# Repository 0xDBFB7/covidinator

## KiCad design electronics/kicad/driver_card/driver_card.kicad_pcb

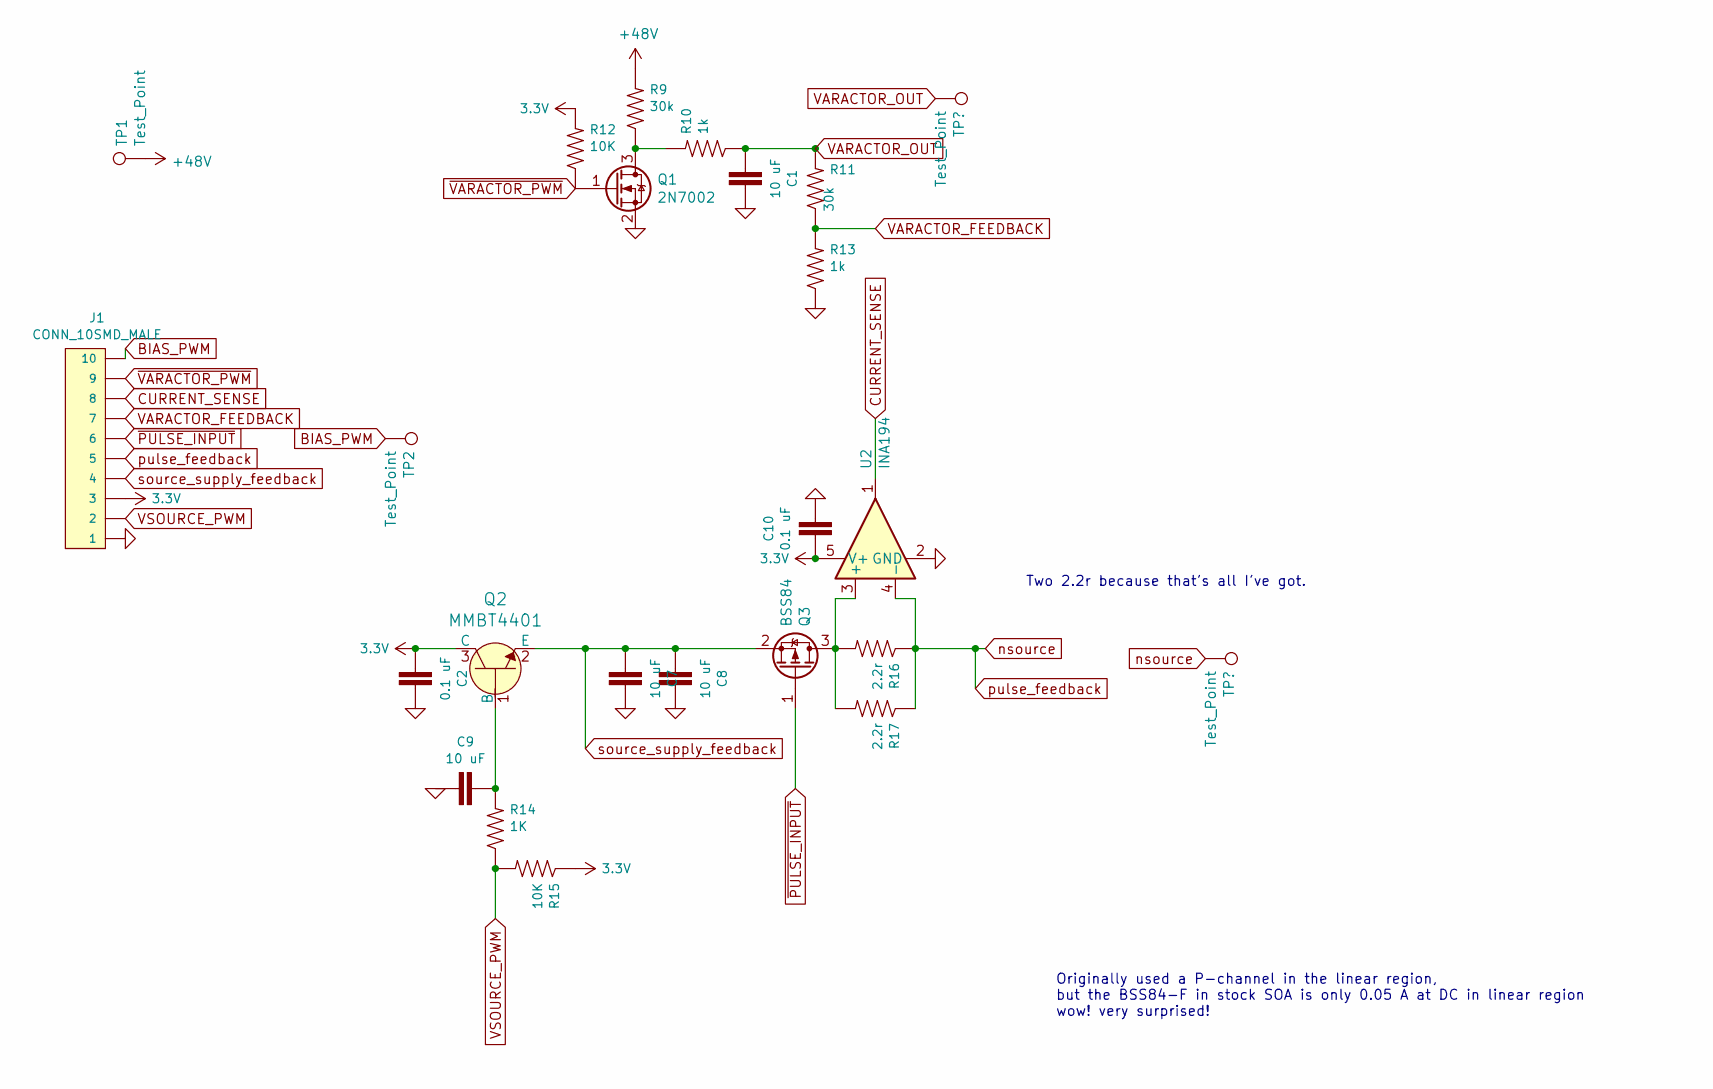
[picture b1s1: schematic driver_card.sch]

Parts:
C1, C7, C8, C9: 10 uF; 0603
C2, C10: 0.1 uF; 0603
J1: CONN_10SMD_MALE; 1X10_SMD_MALE
Q1: 2N7002; SOT-23
Q2: MMBT4401; SOT-23-3; MPN MMBT4401; Digi-Key_PN MMBT4401FSCT-ND
Q3: BSS84; SOT-23
R9, R11: 30k; R_0603_1608Metric
R10, R13: 1k; R_0603_1608Metric
R12: 10K; R_0603_1608Metric
R14: 1K; R_0402_1005Metric
R15: 10K; R_0402_1005Metric
R16, R17: 2.2r; R_0805_2012Metric
TP1, TP2: Test_Point; TestPoint_Pad_2.0x2.0mm
U2: INA194; SOT-23-5

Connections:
3.3V: C2.2, C10.2, J1.3, Q2.3 (C), R12.2, R15.1, U2.5 (V+)
+48V: R9.2, TP1.1
BIAS_PWM: J1.10, TP2.1
CURRENT_SENSE: J1.8, U2.1
GND: C1.1, C2.1, C7.1, C8.1, C9.2, C10.1, J1.1, Q1.2 (S), R13.1, U2.2 (GND)
unnamed: C9.1, Q2.1 (B), R14.2
unnamed: Q1.3 (D), R9.1, R10.2
unnamed: Q3.3 (D), R16.2, R17.2, U2.3 (+)
VARACTOR_FEEDBACK: J1.7, R11.1, R13.2
VARACTOR_OUT: C1.2, R10.1, R11.2; also elsewhere on the board
VSOURCE_PWM: J1.2, R14.1, R15.2
nsource: J1.5, R16.1, R17.1, U2.4 (-); also elsewhere on the board
source_supply_feedback: C7.2, C8.2, J1.4, Q2.2 (E), Q3.2 (S)
~PULSE_INPUT: J1.6, Q3.1 (G)
~VARACTOR_PWM: J1.9, Q1.1 (G), R12.1

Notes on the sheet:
Two 2.2r because that's all I've got.
Originally used a P-channel in the linear region, but the BSS84-F in stock SOA is only 0.05 A at DC in linear region wow! very surprised!

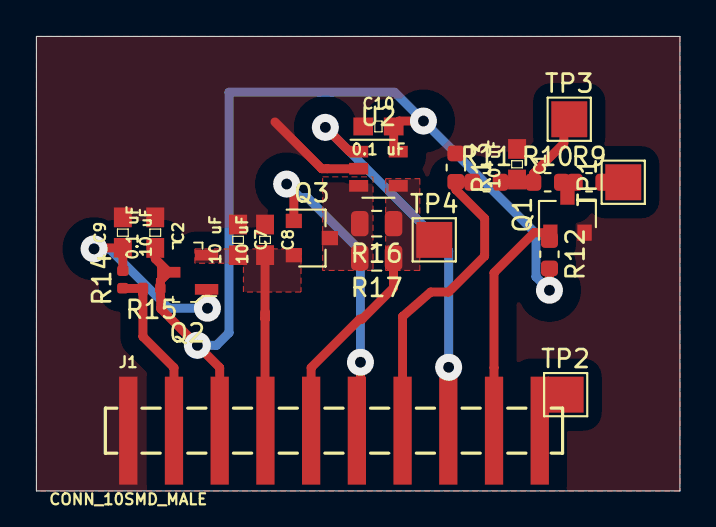
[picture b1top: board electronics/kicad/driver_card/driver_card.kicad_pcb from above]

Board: 2 copper layers, 35.8 x 25.2 mm, 24 parts (0 on the bottom side), 15 nets.

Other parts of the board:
TP3, TP4: Test_Point; TestPoint_Pad_2.0x2.0mm

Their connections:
VARACTOR_OUT: TP3.1; also elsewhere on the board
nsource: TP4.1; also elsewhere on the board

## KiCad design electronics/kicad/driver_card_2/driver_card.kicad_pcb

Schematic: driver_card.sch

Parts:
C1, C2, C3, C8, C10, C11: 0.1 uF; 0603
C4, C9: 10 uF; 0603
C5, C6, C7: 10uF; 1206
J1: CONN_10SMD_MALE; 1X10_SMD_MALE
Q1, Q2, Q4: 2N7002; SOT-23
Q3: BSS84; SOT-23
R1, R9, R11: 30k; R_0603_1608Metric
R2, R18, R19: 10k; R_0603_1608Metric
R3, R7, R8: 5k; R_0603_1608Metric
R4, R10: 1K; R_0603_1608Metric
R5, R6: 2k; R_0603_1608Metric
R12, R13, R14, R15, R17: 1k; R_0603_1608Metric
R16: 0.1R; R_0805_2012Metric
TP1: 48V; TestPoint_Pad_2.0x2.0mm
TP2: 12V; TestPoint_Pad_2.0x2.0mm
TP3, TP4: Test_Point; TestPoint_Pad_2.0x2.0mm
U1: MCP4725SOT-23; SOT23-6
U2: INA194; SOT-23-5
U3: AZ1117CH-3_3TRG1; SOT-223; MPN AZ1117CH-3.3TRG1; Digi-Key_PN AZ1117CH-3.3TRG1DICT-ND
U4: MCP1416T-E_OT; SOT-753; MPN MCP1416T-E/OT; Digi-Key_PN MCP1416T-E/OTCT-ND

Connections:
3.3V: C10.2, J1.3, R5.2, R13.2, U2.5 (V+)
+12V: C2.2, C5.1, R1.2, TP2.1, U3.3, U4.2 (VDD)
+48V: C3.2, R9.2, TP1.1
BIAS_OUT: C11.2, Q4.3 (D), R18.1, R19.2
BIAS_PWM: J1.10, R12.1
CURRENT_SENSE: J1.8, U2.1
GND: C1.1, C2.1, C3.1, C4.1, C5.2, C6.2, C7.2, C8.1, C9.1, C10.1, C11.1, J1.1, Q1.2 (S), Q2.2 (S), Q4.2 (S), R4.1, R6.1, R10.1, R11.1, R17.1, R19.1, U2.2 (GND), U4.4 (GND)
unnamed: C4.2, Q1.1 (G), R5.1, R6.2, R7.2
unnamed: C6.1, R1.1, R2.2, U3.1
unnamed: C7.1, C8.2, Q3.2 (S), R3.2, U3.2, U3.4
unnamed: C9.2, Q4.1 (G), R12.2, R14.1, R15.2
unnamed: Q2.3 (D), R2.1
unnamed: Q3.1 (G), U4.5 (OUT)
unnamed: Q3.3 (D), R16.2, U2.3 (+)
unnamed: R13.1, R14.2
unnamed: R15.1, R17.2
VARACTOR_FEEDBACK: J1.7
VARACTOR_OUT: C1.2, Q1.3 (D), R9.1, R11.2, TP3.1
VSOURCE_PWM: J1.2, Q2.1 (G)
nsource: R8.2, R16.1, R18.2, TP4.1, U2.4 (-)
pulse_feedback: J1.5, R8.1, R10.2
source_supply_feedback: J1.4, R3.1, R4.2
~PULSE_INPUT: J1.6, U4.3 (IN)
~VARACTOR_INPUT: R7.1
~VARACTOR_PWM: J1.9

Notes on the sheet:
Originally used a P-channel in the linear region, but, surprisingly, at 3.3v, the Safe Operating Area at DC of the BSS84-F only goes up to 50 mA.

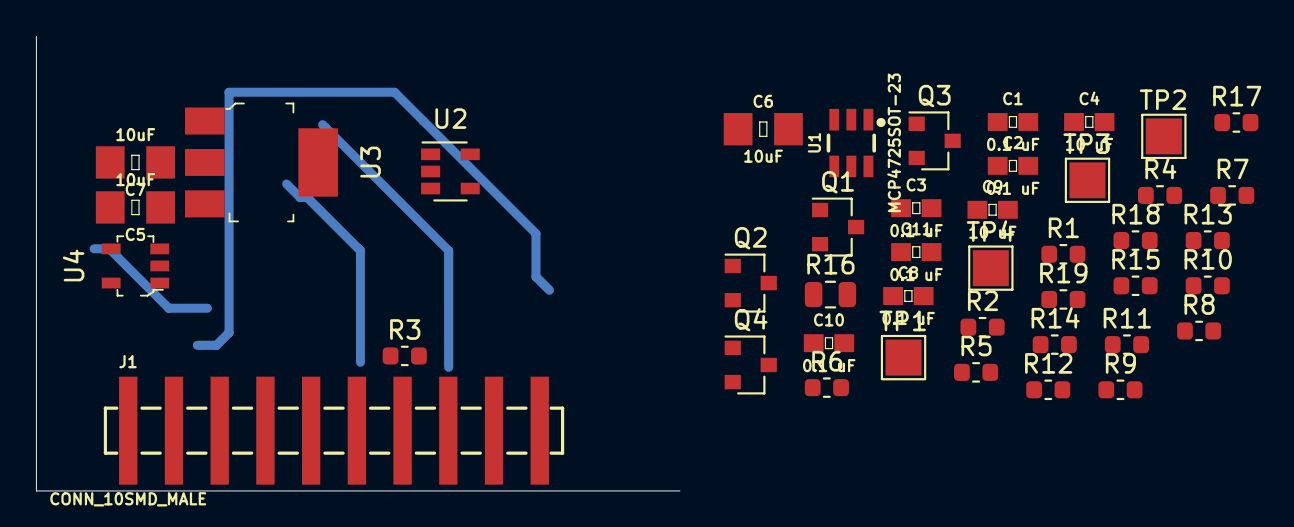
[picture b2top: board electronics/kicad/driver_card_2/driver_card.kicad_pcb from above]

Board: 2 copper layers, 43 parts (0 on the bottom side), 22 nets.

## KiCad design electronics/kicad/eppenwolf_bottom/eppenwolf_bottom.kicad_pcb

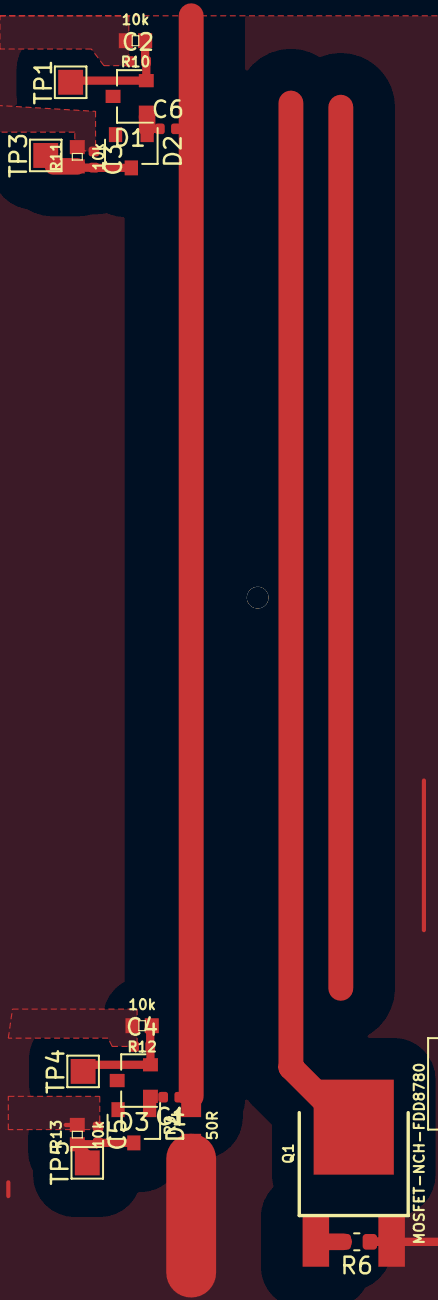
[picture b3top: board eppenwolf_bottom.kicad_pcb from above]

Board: 2 copper layers, 21 parts (0 on the bottom side), 9 nets.

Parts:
C1, C2, C3, C4, C5, C6: 100 pF; C_0402_1005Metric
D1, D2, D3, D4: BAT15-04; SOT-23
Q1: MOSFET-NCH-FDD8780; DPAK
R6: 1k; R_0603_1608Metric
R9: 50R; 0805
R10, R11, R12, R13: 10k; 0402
TP1, TP3, TP4, TP5: capacitance_sensing; TestPoint_Pad_1.5x1.5mm

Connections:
GND: C2.1, C3.1, C4.1, C5.1, Q1.3, R6.1, R9.1, R10.2, R11.2, R12.2, R13.2
unnamed: C1.2, D3.1, D4.1
unnamed: C6.1, D1.1, D2.1
unnamed: Q1.1, R6.2
RF_input: C1.1, C6.2, R9.2
input_power_sense_1: C3.2, D2.3, R11.1, TP3.1
input_power_sense_2: C2.2, D1.2, R10.1, TP1.1
terminated_end_power_sense_1: C5.2, D4.3, R13.1, TP5.1
terminated_end_power_sense_2: C4.2, D3.2, R12.1, TP4.1

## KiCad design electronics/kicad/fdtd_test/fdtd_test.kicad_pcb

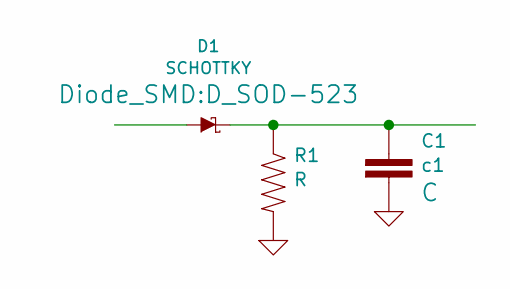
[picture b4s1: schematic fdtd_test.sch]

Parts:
C1: c1; 0402
D1: SCHOTTKY; D_SOD-523
R1: R; 0402

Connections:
GND: C1.2, R1.2
unnamed: C1.1, D1.2 (K), R1.1

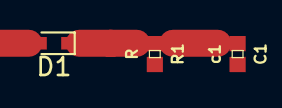
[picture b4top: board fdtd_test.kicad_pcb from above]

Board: 2 copper layers, 3 parts (0 on the bottom side), 2 nets.

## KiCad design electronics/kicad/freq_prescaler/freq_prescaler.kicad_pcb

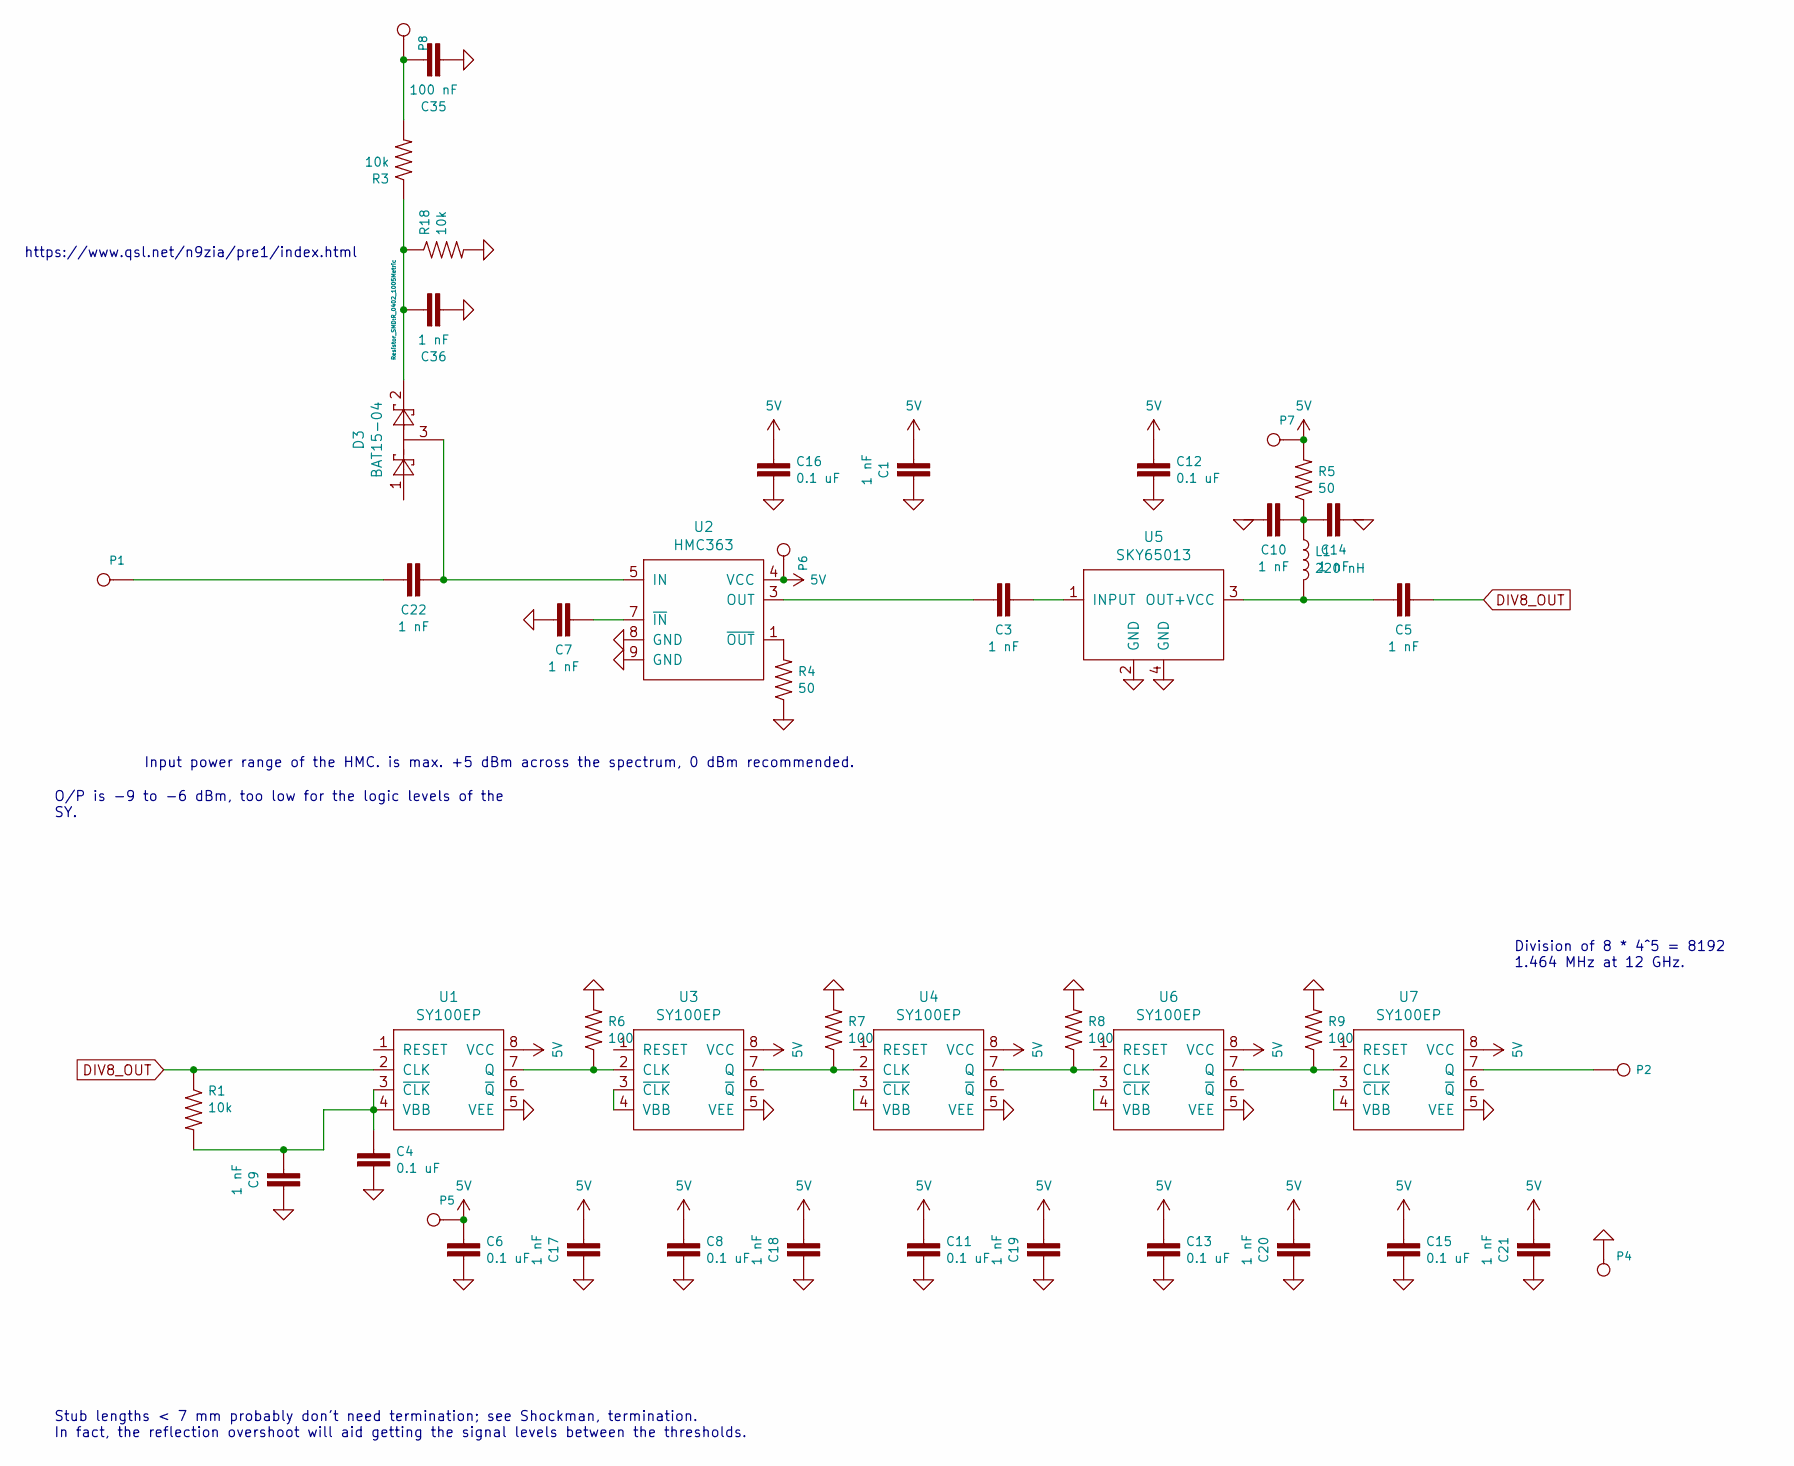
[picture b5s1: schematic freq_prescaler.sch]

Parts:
C1, C3, C5, C7, C9, C10, C14, C17, C18, C19, C20, C21, C22: 1 nF; C_0402_1005Metric
C4, C6, C8, C11, C12, C13, C15, C16: 0.1 uF; 0603
C35: 100 nF; 0603
C36: 1 nF; R_0402_1005Metric
D3: BAT15-04; SOT-23
L1: 220 nH; C_0402_1005Metric
P1: CONN_1; TestPoint_Pad_1.0x1.0mm
P2, P4: OUTPUT; TestPoint_Pad_2.5x2.5mm
P5, P7: CONN_1; TestPoint_Pad_2.5x2.5mm
P6: CONN_1; TestPoint_Pad_1.5x1.5mm
P8: a; TestPoint_Pad_2.5x2.5mm
R1: 10k; C_0402_1005Metric
R3, R18: 10k; R_0402_1005Metric
R4, R5: 50; 0805
R6, R7, R8, R9: 100; 0805
U1, U3, U4, U6, U7: SY100EP; SOIC-8_3.9x4.9mm_P1.27mm
U2: HMC363; SOIC-8-1EP_3.9x4.9mm_P1.27mm_EP2.35x2.35mm
U5: SKY65013; SOT-89-3_Handsoldering

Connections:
5V: C1.2, C6.1, C8.1, C11.1, C12.1, C13.1, C15.1, C16.1, C17.2, C18.2, C19.2, C20.2, C21.2, P5.1, P6.1, P7.1, R5.2, U1.8 (VCC), U2.4 (VCC), U3.8 (VCC), U4.8 (VCC), U6.8 (VCC), U7.8 (VCC)
DIV8_OUT: C5.1, R1.1, U1.2 (CLK)
GND: C1.1, C4.2, C6.2, C7.2, C8.2, C9.1, C10.2, C11.2, C12.2, C13.2, C14.1, C15.2, C16.2, C17.1, C18.1, C19.1, C20.1, C21.1, C35.2, C36.2, P4.1, R4.1, R6.2, R7.2, R8.2, R9.2, R18.2, U1.5 (VEE), U2.8 (GND), U2.9 (GND), U3.5 (VEE), U4.5 (VEE), U5.2 (GND), U5.4 (GND), U6.5 (VEE), U7.5 (VEE)
unnamed: C3.1, U5.1 (INPUT)
unnamed: C3.2, U2.3 (OUT)
unnamed: C4.1, C9.2, R1.2, U1.3 (~CLK), U1.4 (VBB)
unnamed: C5.2, L1.2, U5.3 (OUT+VCC)
unnamed: C7.1, U2.7 (~IN)
unnamed: C10.1, C14.2, L1.1, R5.1
unnamed: C22.1, D3.3, U2.5 (IN)
unnamed: C22.2, P1.1
unnamed: C35.1, P8.1, R3.2
unnamed: C36.1, D3.2, R3.1, R18.1
unnamed: P2.1, U7.7 (Q)
unnamed: R4.2, U2.1 (~OUT)
unnamed: R6.1, U1.7 (Q), U3.2 (CLK)
unnamed: R7.1, U3.7 (Q), U4.2 (CLK)
unnamed: R8.1, U4.7 (Q), U6.2 (CLK)
unnamed: R9.1, U6.7 (Q), U7.2 (CLK)
unnamed: U3.3 (~CLK), U3.4 (VBB)
unnamed: U4.3 (~CLK), U4.4 (VBB)
unnamed: U6.3 (~CLK), U6.4 (VBB)
unnamed: U7.3 (~CLK), U7.4 (VBB)

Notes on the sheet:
Input power range of the HMC. is max. +5 dBm across the spectrum, 0 dBm recommended.
O/P is -9 to -6 dBm, too low for the logic levels of the SY.
Division of 8 * 4^5 = 8192 1.464 MHz at 12 GHz.
Stub lengths < 7 mm probably don't need termination; see Shockman, termination. In fact, the reflection overshoot will aid getting the signal levels between the thresholds.
https://www.qsl.net/n9zia/pre1/index.html

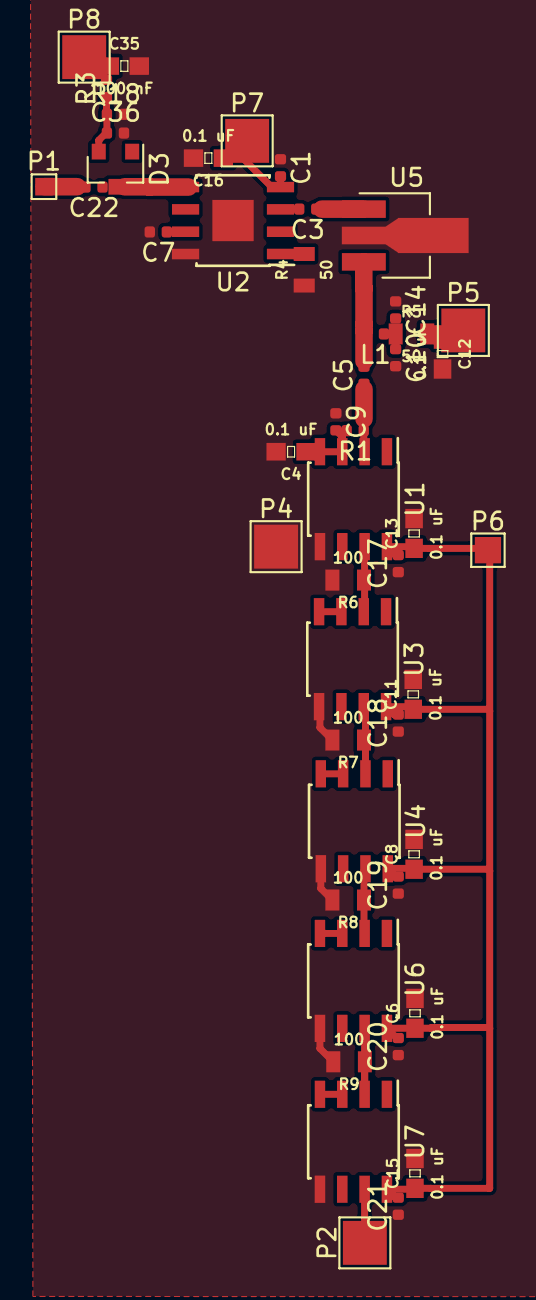
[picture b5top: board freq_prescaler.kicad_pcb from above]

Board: 2 copper layers, 48 parts (0 on the bottom side), 23 nets.

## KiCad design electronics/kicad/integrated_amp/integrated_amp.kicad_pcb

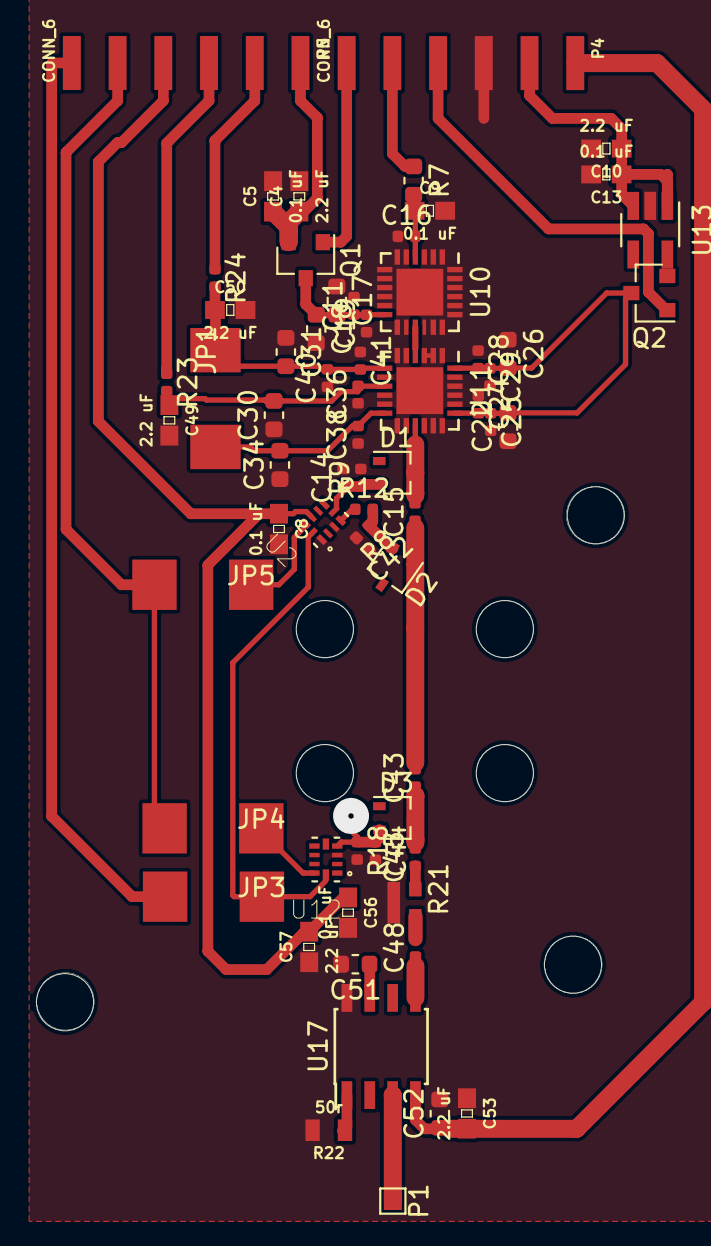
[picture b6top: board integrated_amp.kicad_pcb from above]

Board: 2 copper layers, 65 parts (0 on the bottom side), 30 nets.

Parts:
C4, C10, C49, C50, C53, C57: 2.2 uF; 0603
C5, C8, C9, C13, C56: 0.1 uF; 0603
C11, C16, C19, C24, C25, C28, C29, C36, C38, C40, C41: 1 nF; C_0402_1005Metric
C14, C15, C42, C43, C44, C45, C48: 1 nF; R_0402_1005Metric
C17, C18, C22, C26, C51, C52: 1 nF; C_0603_1608Metric
C30, C31, C34: 0.1 uF; C_0603_1608Metric
D1, D2, D3: BAT15-04; SOT-323_SC-70
JP1, JP3, JP4, JP5: Jumper; JUMPER_5102
P1: CONN_1; TestPoint_Pad_1.0x1.0mm
P4, P5: CONN_6; 1X06-SMD_RA_MALE
Q1, Q2: DMP3099L; SOT-23
R7: 10k; R_0603_1608Metric
R8, R9, R12, R18, R23, R24: 10k; R_0402_1005Metric
R21: attenuator; PAT1220
R22: 50r; 0805
U2, U12: ADS1115IDGS; IC_ADS1115IRUGR
U10: HMC732; QFN-24-1EP_4x4mm_P0.5mm_EP2.6x2.6mm
U11: HMC996; QFN-24-1EP_4x4mm_P0.5mm_EP2.6x2.6mm
U13: MAX4915; SOT-23-5_HandSoldering
U17: HMC363; SOIC-8_3.9x4.9mm_P1.27mm

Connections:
3.3V: C8.1, C56.1, C57.2, P5.4, U2.8, U12.1, U12.8
5V: C4.1, C5.1, C10.1, C13.1, C52.1, C53.2, P4.1, P4.2, P5.1, Q1.2, U13.1, U13.3, U17.4
AMP_DRAIN_CONTROL_: P4.4, Q2.1
AMP_DRAIN_SUPPLY: C22.2, C24.2, C25.1, C26.2, C28.2, C29.1, Q2.3, U11.19, U11.24
AMP_GAIN_CONTROL: C30.2, C36.2, C49.1, R23.2, U11.9
AMP_GAIN_CONTROL_: P5.3, R23.1
AMP_GATE_CONTROL: C31.2, C34.2, C38.2, C40.2, C41.2, C50.1, JP1.1, JP1.2, R24.2, U11.7, U11.12
AMP_GATE_CONTROL_: P5.2, R24.1
GND: C4.2, C5.2, C8.2, C9.2, C10.2, C11.2, C13.2, C14.2, C16.1, C17.1, C18.2, C19.1, C22.1, C24.1, C25.2, C26.1, C28.1, C29.2, C30.1, C31.1, C34.1, C36.1, C38.1, C40.1, C41.1, C42.2, C44.2, C49.2, C50.2, C51.2, C52.2, C53.1, C56.2, C57.1, P4.3, R8.2, R9.2, R18.2, R21.3, R22.2, U2.1, U2.3, U10.1, U10.2, U10.3, U10.5, U10.6, U10.7, U10.8, U10.9, U10.10, U10.11, U10.13, U10.14, U10.16, U10.17, U10.18, U10.19, U10.20, U10.21, U10.22, U10.23, U10.24, U10.25, U11.1, U11.2, U11.3, U11.5, U11.6, U11.8, U11.10, U11.11, U11.13, U11.14, U11.16, U11.17, U11.18, U11.20, U11.21, U11.22, U11.23, U11.25, U12.3, U13.2, U17.8
unnamed: C14.1, D1.2, R9.1, U2.5
unnamed: C15.1, C43.2, D2.1
unnamed: C15.2, D1.3, U11.15
unnamed: C9.1, C16.2, R7.2, U10.4
unnamed: C42.1, D2.2, R8.1
unnamed: C43.1, C45.2, D3.3
unnamed: C44.1, D3.2, R18.1, U12.4
unnamed: C45.1, R21.1
unnamed: C48.1, U17.5
unnamed: C48.2, R21.2
unnamed: C51.1, U17.7
unnamed: P1.1, U17.3
unnamed: Q2.2, U13.5
unnamed: R12.1, U2.4
unnamed: R22.1, U17.1
unnamed: U10.15, U11.4
SCL: JP3.1, JP3.2, P5.6, U2.10, U12.10
SDA: JP4.1, JP4.2, JP5.1, JP5.2, P5.5, U2.9, U12.9
VCO_POWER: C11.1, C17.2, C18.1, C19.2, Q1.3, U10.12
VCO_POWER_CONTROL_: P4.6, Q1.1
Vtune: P4.5, R7.1

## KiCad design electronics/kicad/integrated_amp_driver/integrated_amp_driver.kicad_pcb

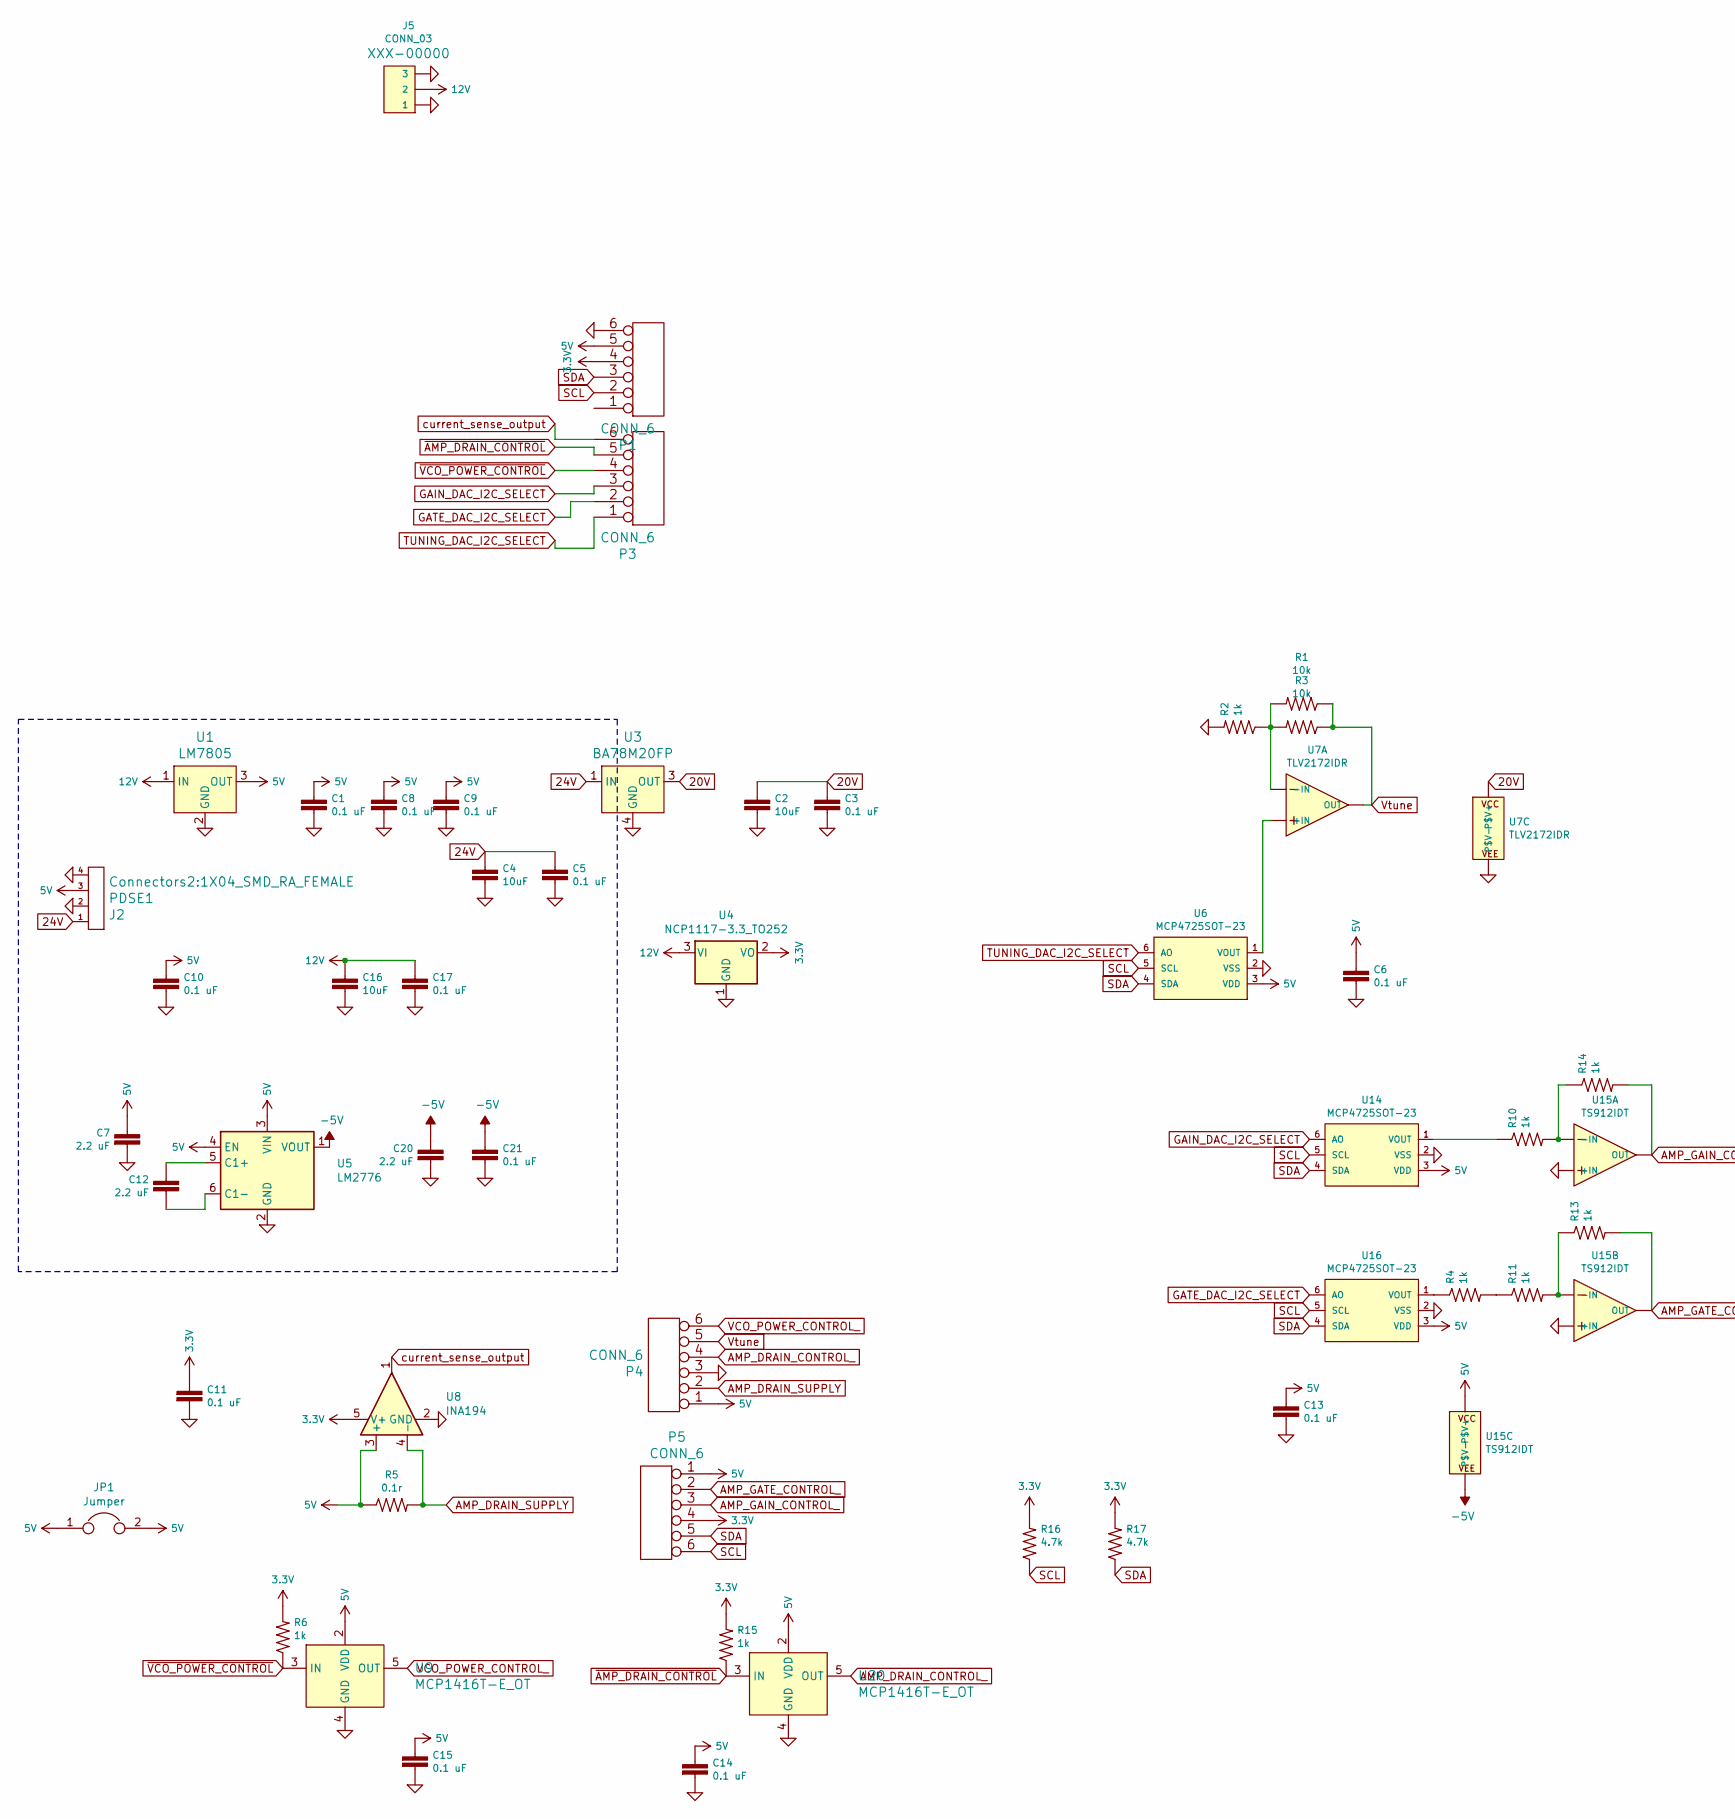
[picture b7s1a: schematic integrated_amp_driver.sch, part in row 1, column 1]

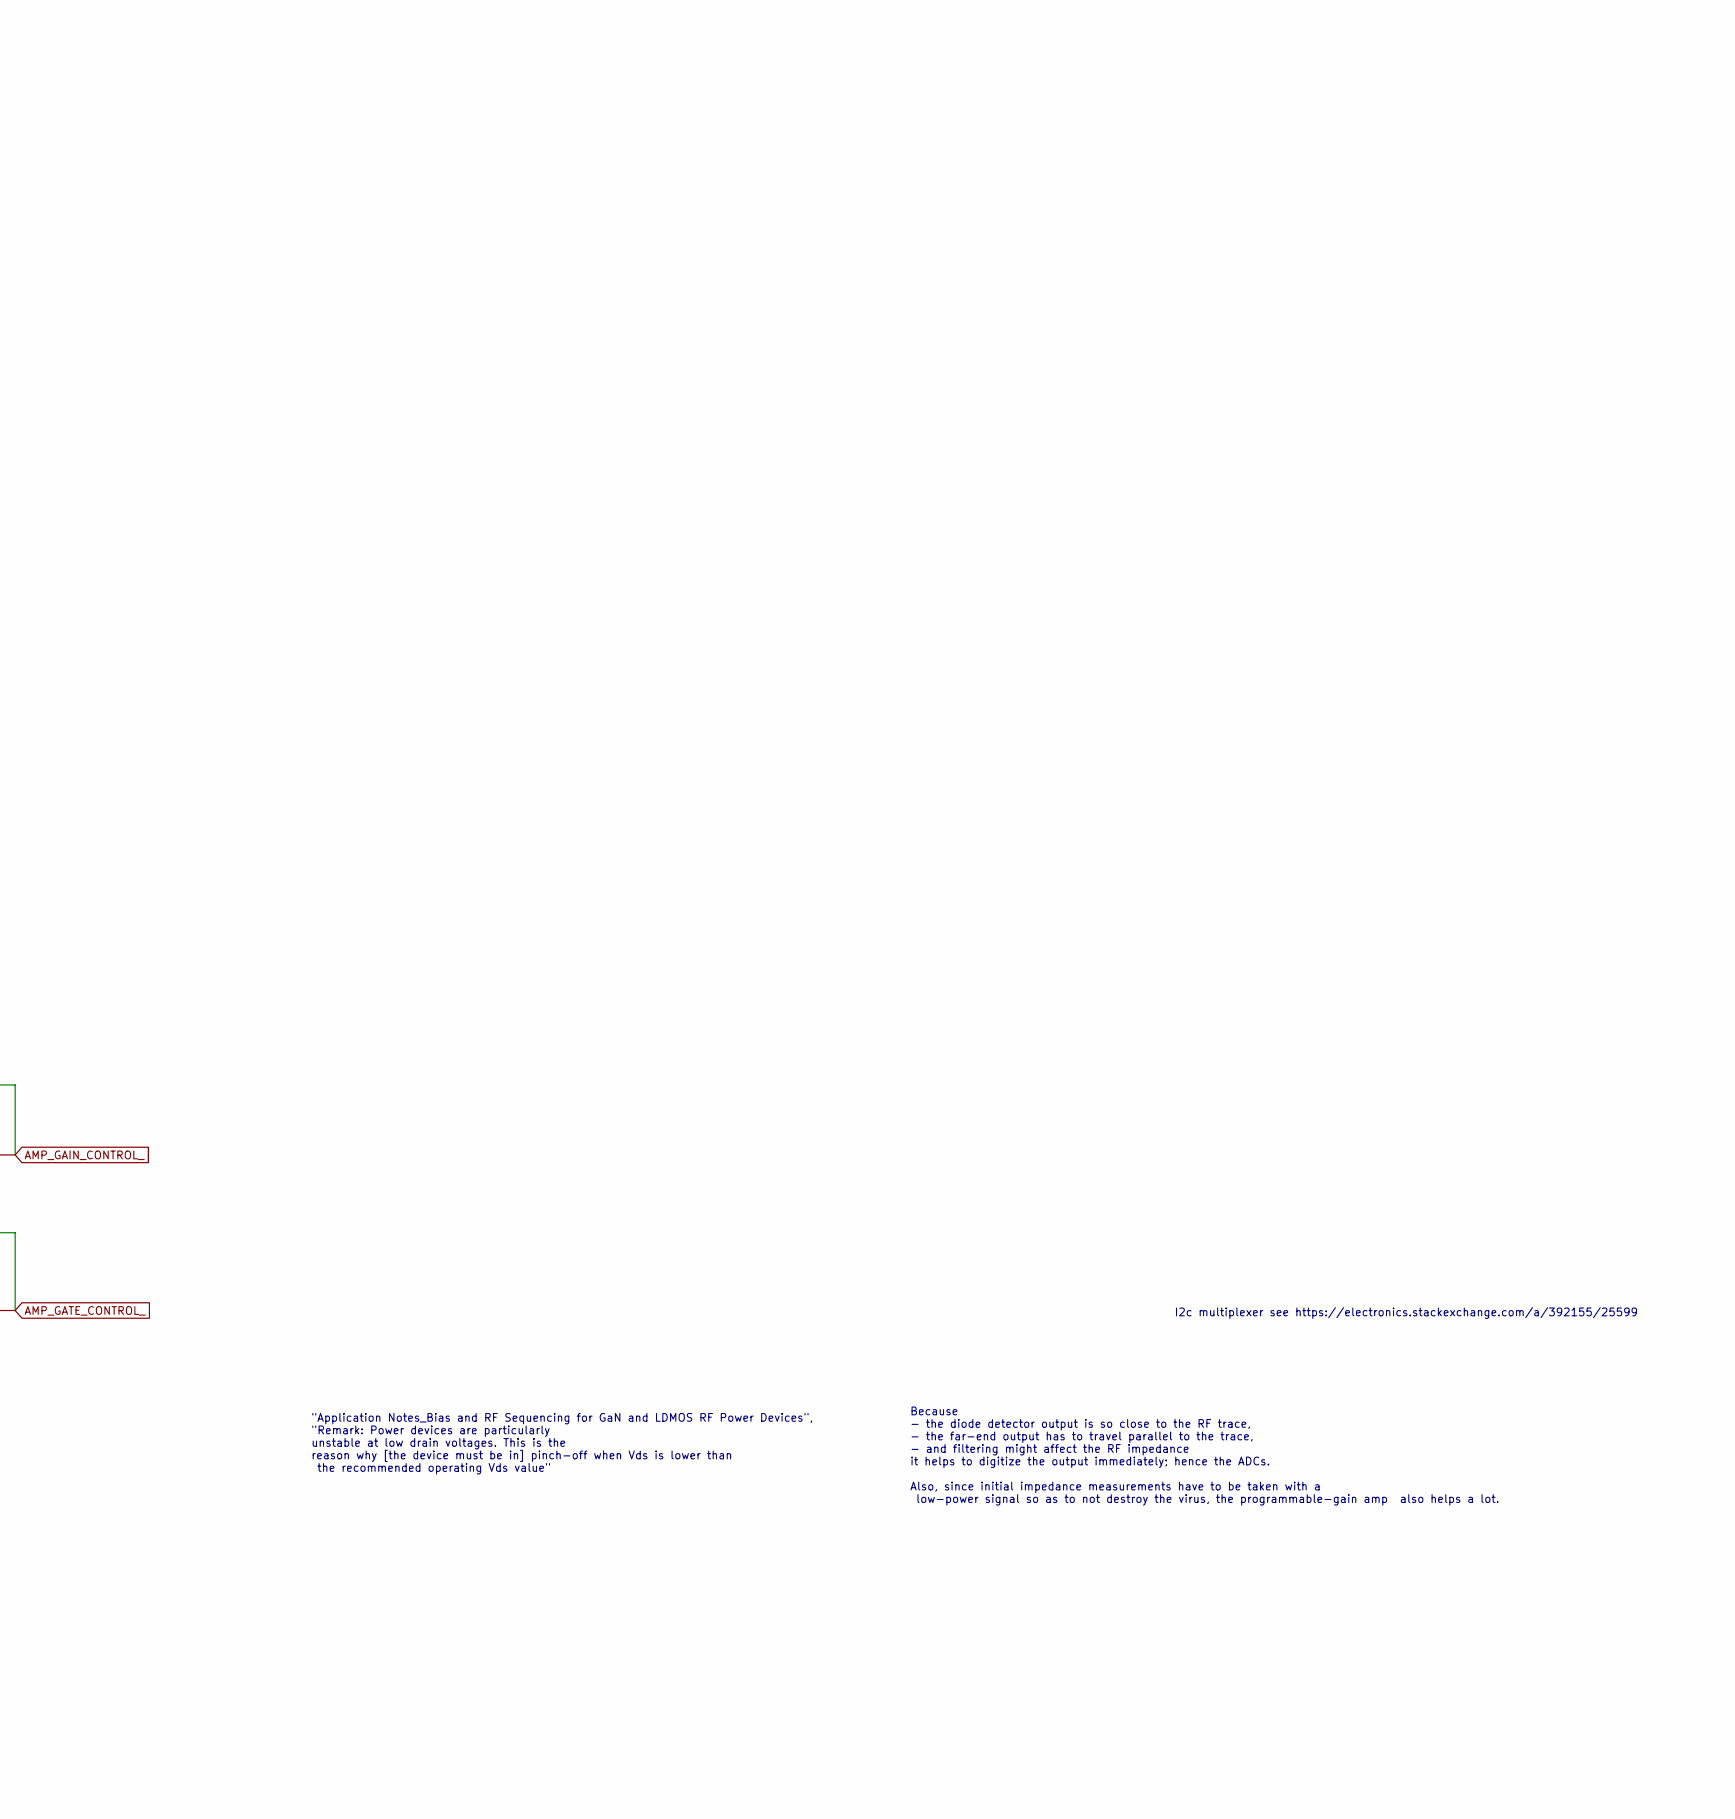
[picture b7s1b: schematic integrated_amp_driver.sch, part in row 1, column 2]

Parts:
C1, C3, C5, C6, C8, C9, C10, C11, C13, C14, C15, C17, C21: 0.1 uF; 0603
C2, C4, C16: 10uF; 1206
C7, C12, C20: 2.2 uF; 0603
J2: PDSE1; 1X04_SMD_RA_FEMALE
J5: CONN_03; 1X03_SMD_RA_MALE
JP1: Jumper; JUMPER_5102
P1, P3, P4, P5: CONN_6; 1X06-SMD_RA_MALE
R1, R3: 10k; R_0603_1608Metric
R2, R4, R6, R10, R11, R13, R14, R15: 1k; R_0603_1608Metric
R5: 0.1r; 0805
R16, R17: 4.7k; R_0603_1608Metric
U1: LM7805; SOT-223; MPN LM7812CT; Digi-Key_PN LM7812CTFS-ND
U3: BA78M20FP; TO-252-3; MPN MC7805BDTRKG; Digi-Key_PN MC7805BDTRKGOSCT-ND
U4: NCP1117-3.3_TO252; TO-252-2
U5: LM2776; SOT-23-6
U6, U14, U16: MCP4725SOT-23; SOT23-6
U7: TLV2172IDR; SOIC-8_3.9x4.9mm_P1.27mm
U8: INA194; SOT-23-5
U9, U20: MCP1416T-E_OT; SOT-753; MPN MCP1416T-E/OT; Digi-Key_PN MCP1416T-E/OTCT-ND
U15: TS912IDT; SOIC-8_3.9x4.9mm_P1.27mm

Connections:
3.3V: C11.1, P1.4, P5.4, R6.2, R15.2, R16.2, R17.2, U4.2 (VO), U8.5 (V+)
5V: C1.1, C6.1, C7.1, C8.1, C9.1, C10.1, C13.1, C14.1, C15.1, J2.3, JP1.1, JP1.2, P1.5, P4.1, P5.1, R5.1, U1.3 (OUT), U5.3 (VIN), U5.4 (EN), U6.3 (VDD), U8.3 (+), U9.2 (VDD), U14.3 (VDD), U15.8 (P$V+), U16.3 (VDD), U20.2 (VDD)
12V: C16.1, C17.1, J5.2, U1.1 (IN), U4.3 (VI)
20V: C2.1, C3.1, U3.3 (OUT), U7.8 (P$V+)
24V: C4.1, C5.1, J2.1, U3.1 (IN)
-5V: C20.1, C21.1, U5.1 (VOUT), U15.4 (P$V-)
AMP_DRAIN_CONTROL_: P4.4, U20.5 (OUT)
AMP_DRAIN_SUPPLY: P4.2, R5.2, U8.4 (-)
AMP_GAIN_CONTROL_: P5.3, R14.2, U15.1 (OUT)
AMP_GATE_CONTROL_: P5.2, R13.2, U15.7 (OUT)
GAIN_DAC_I2C_SELECT: P3.3, U14.6 (AO)
GATE_DAC_I2C_SELECT: P3.2, U16.6 (AO)
GND: C1.2, C2.2, C3.2, C4.2, C5.2, C6.2, C7.2, C8.2, C9.2, C10.2, C11.2, C13.2, C14.2, C15.2, C16.2, C17.2, C20.2, C21.2, J2.2, J2.4, J5.1, J5.3, P1.6, P4.3, R2.2, U1.2 (GND), U3.4 (GND), U4.1 (GND), U5.2 (GND), U6.2 (VSS), U7.4 (P$V-), U8.2 (GND), U9.4 (GND), U14.2 (VSS), U15.3 (+IN), U15.5 (+IN), U16.2 (VSS), U20.4 (GND)
unnamed: C12.1, U5.5 (C1+)
unnamed: C12.2, U5.6 (C1-)
unnamed: R1.2, R2.1, R3.2, U7.2 (-IN)
unnamed: R4.1, U16.1 (VOUT)
unnamed: R10.1, U14.1 (VOUT)
unnamed: R10.2, R14.1, U15.2 (-IN)
unnamed: R4.2, R11.1
unnamed: R11.2, R13.1, U15.6 (-IN)
unnamed: U6.1 (VOUT), U7.3 (+IN)
SCL: P1.2, P5.6, R16.1, U6.5 (SCL), U14.5 (SCL), U16.5 (SCL)
SDA: P1.3, P5.5, R17.1, U6.4 (SDA), U14.4 (SDA), U16.4 (SDA)
TUNING_DAC_I2C_SELECT: P3.1, U6.6 (AO)
VCO_POWER_CONTROL_: P4.6, U9.5 (OUT)
Vtune: P4.5, R1.1, R3.1, U7.1 (OUT)
current_sense_output: P3.6, U8.1
~AMP_DRAIN_CONTROL: P3.5, R15.1, U20.3 (IN)
~VCO_POWER_CONTROL: P3.4, R6.1, U9.3 (IN)

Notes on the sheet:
"Application Notes_Bias and RF Sequencing for GaN and LDMOS RF Power Devices", "Remark: Power devices are particularly unstable at low drain voltages. This is the reason why [the device must be in] pinch-off when Vds is lower than the recommended operating Vds value"
I2c multiplexer see https://electronics.stackexchange.com/a/392155/25599
Because - the diode detector output is so close to the RF trace, - the far-end output has to travel parallel to the trace, - and filtering might affect the RF impedance it helps to digitize the output immediately; hence the ADCs. Also, since initial impedance measurements have to be taken with a lo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

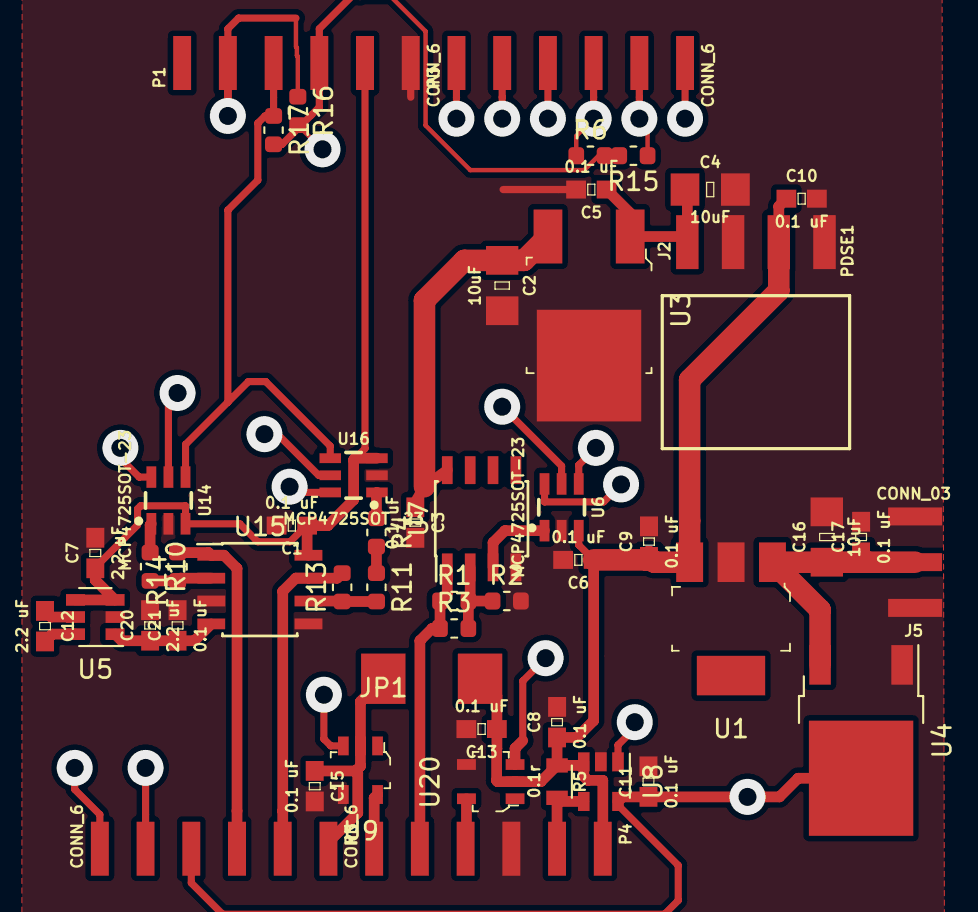
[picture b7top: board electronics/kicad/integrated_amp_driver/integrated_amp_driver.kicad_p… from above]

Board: 2 copper layers, 50 parts (0 on the bottom side), 30 nets.
